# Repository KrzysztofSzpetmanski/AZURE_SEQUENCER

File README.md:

# AZURE_SEQUENCER

Firmware workspace for the AZURE Eurorack module based on Raspberry Pi Pico 2 (RP2350).

Current firmware build: `2.003`

## Current Apps

- `CALIBRATION` - 4-point DAC calibration with two ranges: `-3..+7V` and `0..+10V`
- `NOTES` - calibration point summary view
- `VOLTS` - calibration range and point voltage view
- `GRIDS` - Mutable Grids-style trigger engine with parameter menu and 32-step per-channel preview
- `TRIG SEQ` - trigger sequencer with grid editing, presets and clock options
- `4XEUCLID` - 4-channel Euclidean trigger generator with per-channel steps/hits
- `TR2GATE` - 4-channel trigger-to-gate converter with per-channel source/time/probability
- `TR2ADSR` - 4-channel trigger-to-envelope generator with AR/ASR/ADSR modes

## Build

```bash
cd /Users/lazuli/Documents/PROGRAMMING/RSB_PICO/AZURE_SEQUENCER
cmake -S . -B build
cmake --build build -j4
```

Artifacts:

- `build/hrdw_test.elf`
- `build/hrdw_test.uf2`

## Flash

Standard Pico UF2 drag-and-drop flow:

1. Hold BOOTSEL while connecting Pico 2 via USB.
2. Copy `build/hrdw_test.uf2` to the mounted RPI-RP2 drive.

## Project Structure

- `src/hrdw_test.c` - app loop, UI, app state machines
- `src/hal_io.*` - OLED, encoders, buttons, DAC I/O
- `src/firmware_version.h` - AZURE firmware build label shown in the main menu
- `src/hal_mux_adc.*` - CV MUX ADC input handling
- `src/clock_input.*` - TR1 GPIO IRQ clock event queue and diagnostics
- `src/trigger_output.*` - shared us-based trigger/gate pulse scheduler
- `src/calibration.*` - calibration model + flash persistence
- `src/grids_engine.*` - Grids trigger generation core
- `src/trigseq_engine.*` - trigger sequencer core
- `src/app_settings.*` - app settings persistence
- `hardware/` - KiCad schematic and PCB

## Timing Notes

External clock on `TR1` is timestamped in a GPIO IRQ and delivered to apps through a small event queue. `TRIG SEQ`, `4XEUCLID`, `GRIDS`, and `BURST GEN` consume those events via `*_on_clock_tick(timestamp_us)` style dispatch instead of polling for the clock edge in their UI/update code.

Trigger and burst pulse widths are scheduled in microseconds by the shared trigger output engine. Timing accuracy is limited by MCP4728 I2C update latency; firmware minimizes jitter by using IRQ timestamping, cached output states and batched DAC writes. The DAC bus defaults to 400 kHz via `DAC_I2C_BAUDRATE` in `src/hal_io.c`; set it back to 100000 if a hardware build has marginal pull-ups or bus stability issues.

Pulse OFF service is driven by a 500 us repeating timer flag and serviced from the foreground timing path before OLED/UI work. The timer callback does not write I2C directly; MCP4728 writes stay out of IRQ context.

Optional 1 Hz timing diagnostics can be enabled with `ENABLE_TIMING_DIAG_PRINT` in `src/hrdw_test.c`. The diagnostics include clock IRQ count, ignored edges, queue overflow, measured BPM, max clock-event latency, max trigger-fire latency, DAC write/skip counters, and max OLED frame time.

## Hardware Timing Test Plan

1. Feed a stable master clock or FH-2 clock into `TR1`.
2. Set `TRIG SEQ` to 16 steps with hits on 1/5/9/13.
3. On an oscilloscope, measure `TR1` edge to output trigger latency, pulse width, and jitter while OLED is active and encoders are moved.
4. Test `4XEUCLID` with a stable `4/16` pattern and verify even output spacing.
5. Test `GRIDS` while changing CV/fill; CV sampling should not disturb clock-edge timing.
6. Test fast `BURST GEN` patterns; pulses should not merge or disappear except within MCP4728/I2C limits.
7. Compare DAC/I2C stability at 400 kHz versus 100 kHz if the bus shows artifacts.

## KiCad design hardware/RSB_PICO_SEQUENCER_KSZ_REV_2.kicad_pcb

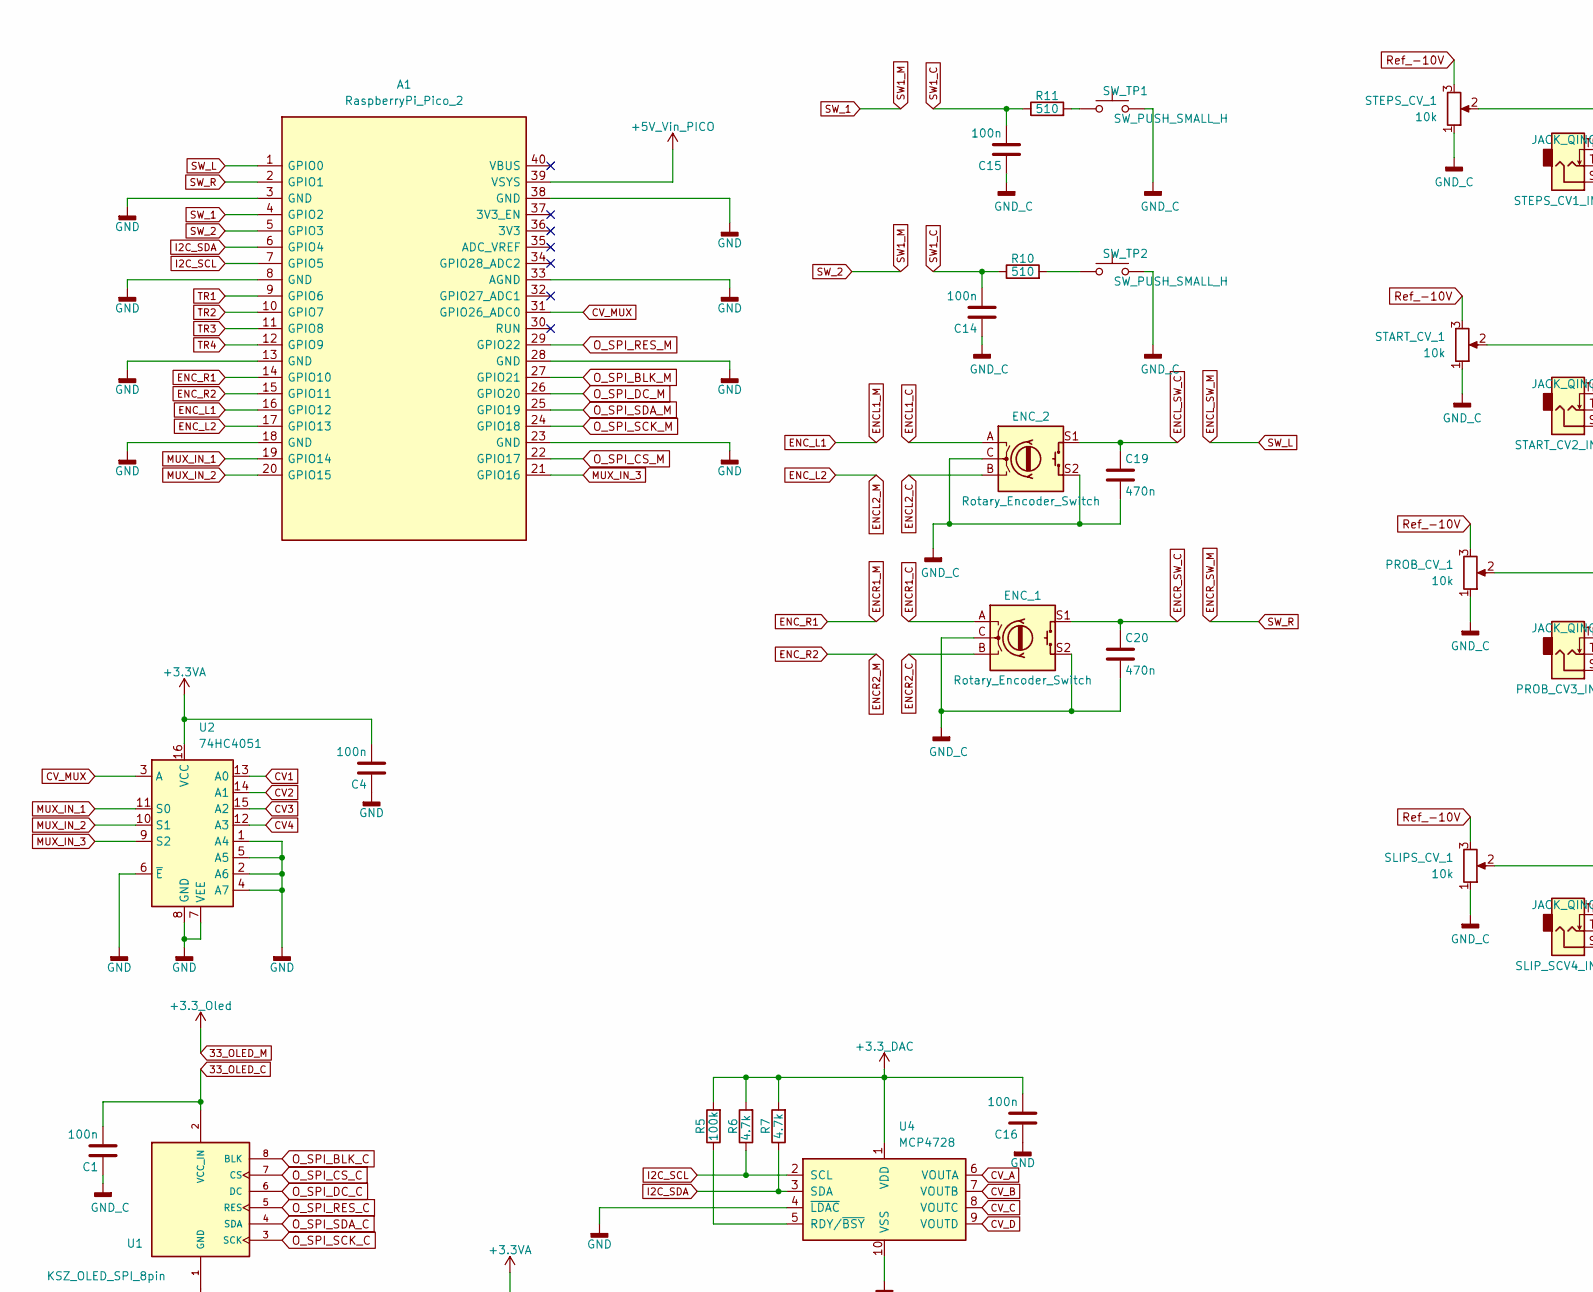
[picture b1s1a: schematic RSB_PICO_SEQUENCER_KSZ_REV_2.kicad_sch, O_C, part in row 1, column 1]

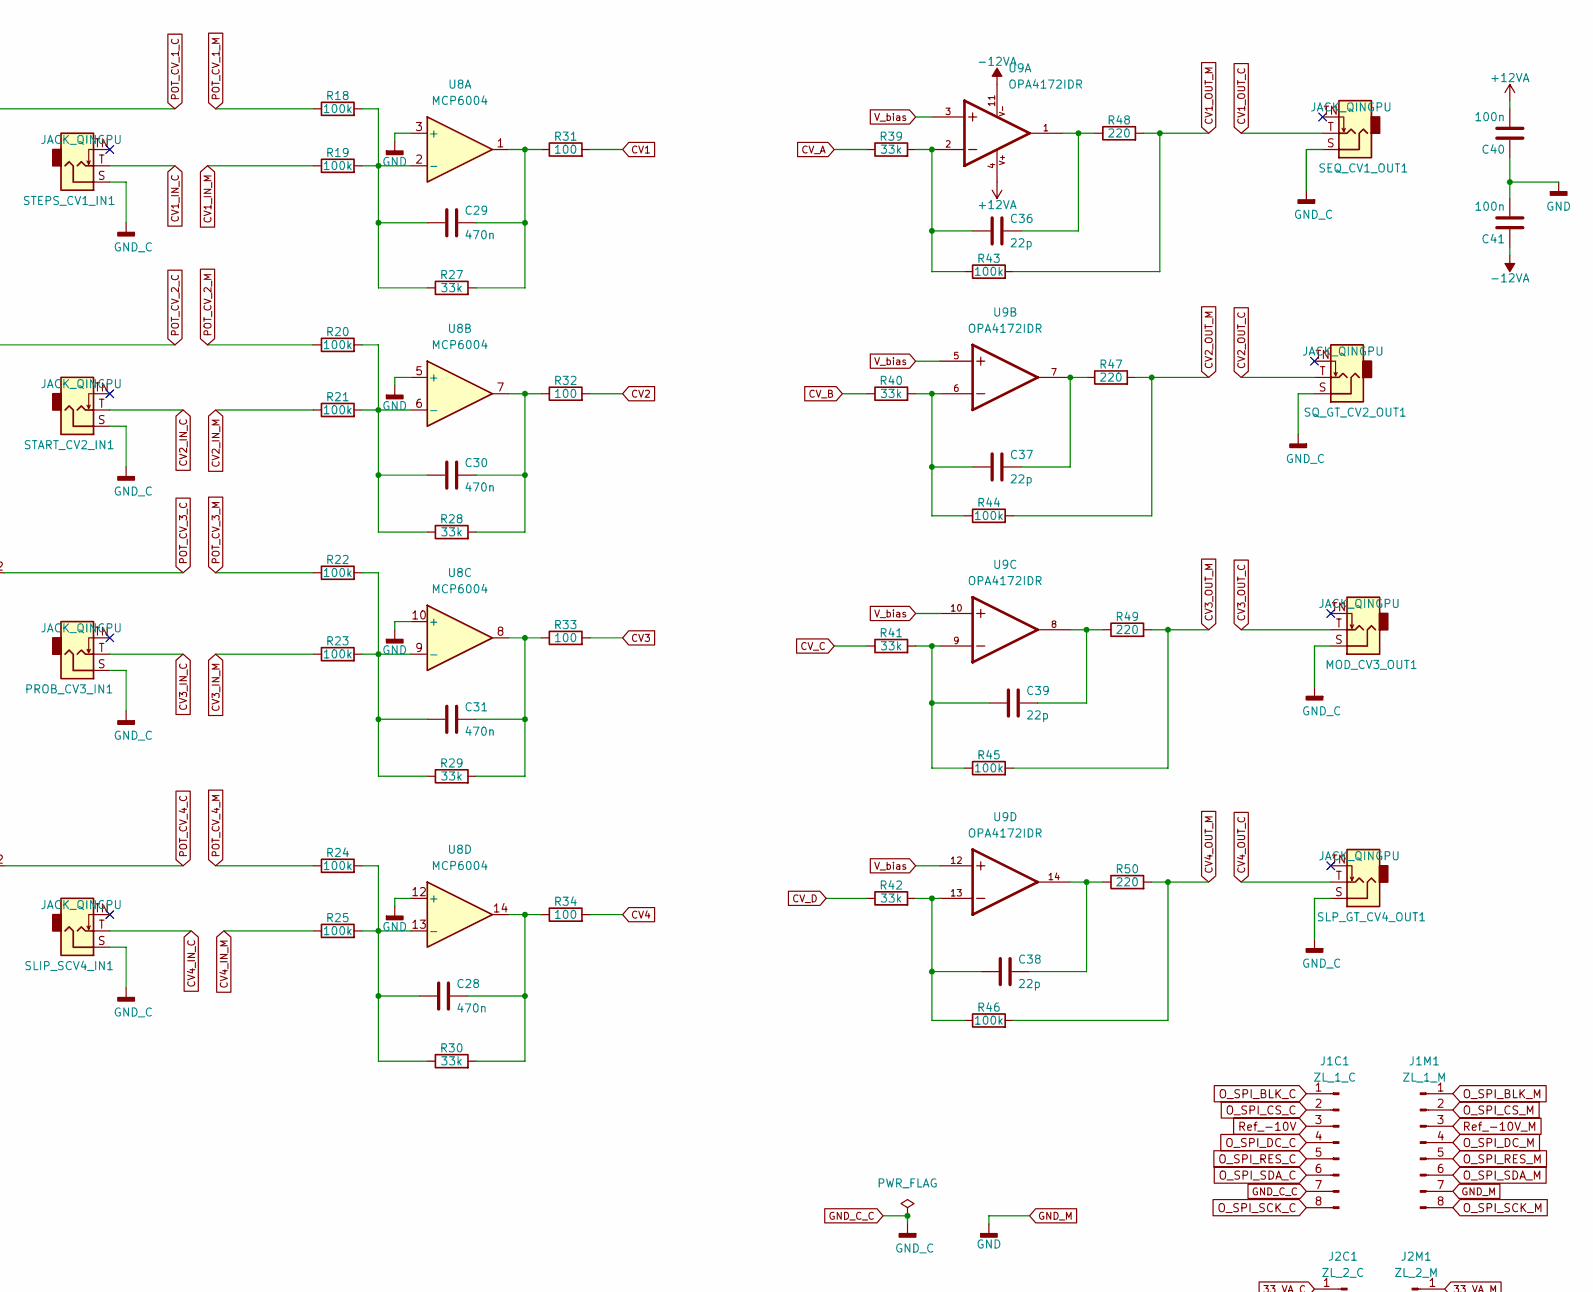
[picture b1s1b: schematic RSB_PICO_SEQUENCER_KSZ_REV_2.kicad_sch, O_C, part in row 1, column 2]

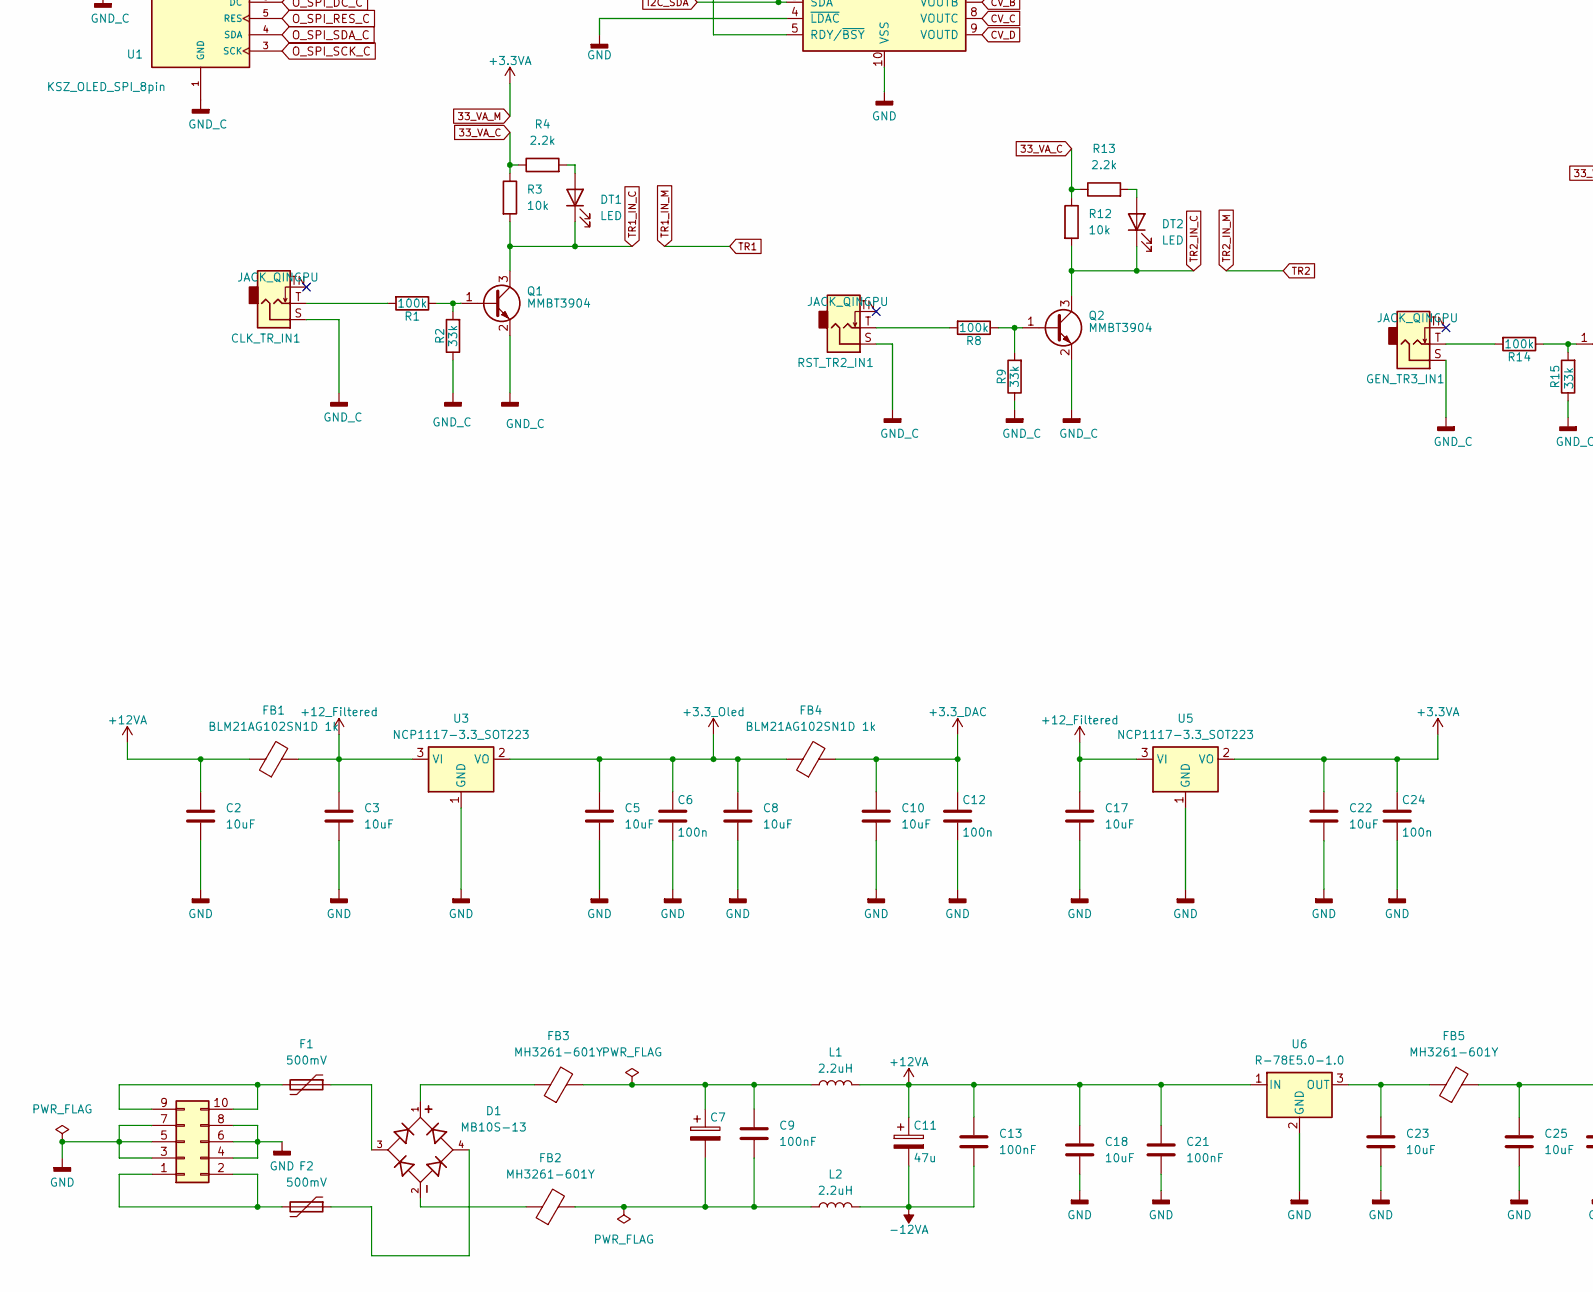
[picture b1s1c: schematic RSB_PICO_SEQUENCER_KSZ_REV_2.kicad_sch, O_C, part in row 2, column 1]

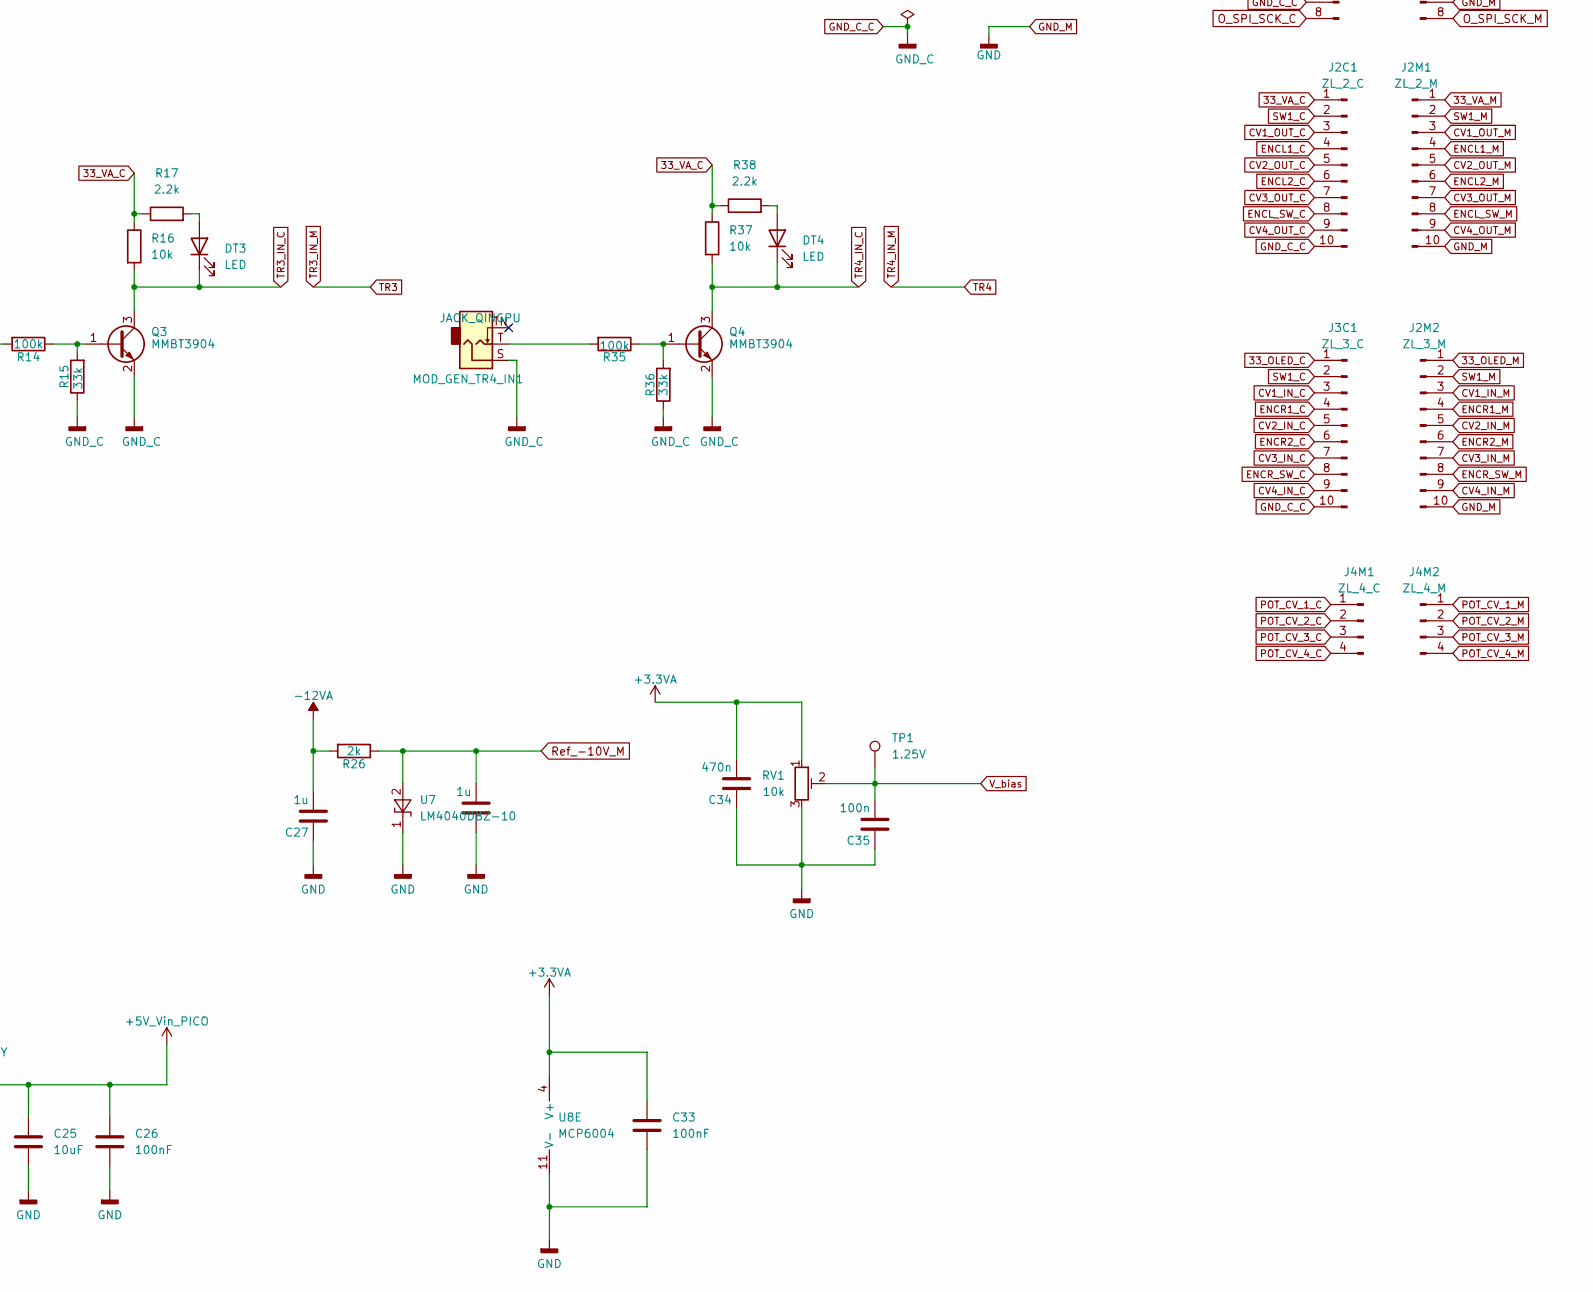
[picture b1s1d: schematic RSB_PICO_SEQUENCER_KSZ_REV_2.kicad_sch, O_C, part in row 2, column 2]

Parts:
A1: RaspberryPi_Pico_2; RaspberryPi_Pico_2_KSZ
C1, C4, C14, C15, C16, C35, C40, C41: 100n; C_0603_1608Metric_Pad1.08x0.95mm_HandSolder; MPN C0603C104Z3VACTU
C2, C3, C5, C8, C10, C17, C18, C22, C23, C25: 10uF; C_1206_3216Metric_Pad1.33x1.80mm_HandSolder
C6, C12, C24: 100n; C_0603_1608Metric_Pad1.08x0.95mm_HandSolder; MPN C0603C104Z3VACTU; LCSC C49678
C7, C11: 47u; CP_Radial_D5.0mm_P2.00mm; MPN EEF-CX1D220R
C9, C13, C21, C26, C33: 100nF; C_0603_1608Metric_Pad1.08x0.95mm_HandSolder; LCSC C49678
C19, C20, C28, C29, C30, C31, C34: 470n; C_0603_1608Metric_Pad1.08x0.95mm_HandSolder; MPN EMK107B7474KA-T
C27, C32: 1u; C_0603_1608Metric_Pad1.08x0.95mm_HandSolder; MPN GCJ188R71E105KA01D
C36, C37, C38, C39: 22p; C_0603_1608Metric_Pad1.08x0.95mm_HandSolder; MPN C0603C220J5GACTU
CLK_TR_IN1: JACK_QINGPU; Jack_3.5mm_tip_switch_thonkiconn
D1: MB10S-13; SOIC245P670X290-4N
DT1, DT2, DT3, DT4: LED; LED_D3.0mm
ENC_1, ENC_2: Rotary_Encoder_Switch; RotaryEncoder_Bourns-PEC11R-4xxxF-Sxxxx-Switch_Vertical_H20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; MPN PEC11S-9215K-H0015
F1, F2: 500mV; C_Disc_D5.0mm_W2.5mm_P5.00mm
FB1, FB4: BLM21AG102SN1D 1k; L_0805_2012Metric_Pad1.05x1.20mm_HandSolder
FB2, FB3, FB5: MH3261-601Y; L_1206_3216Metric
GEN_TR3_IN1: JACK_QINGPU; Jack_3.5mm_tip_switch_thonkiconn
J1: Bus_Power; Power_Header
J1C1: ZL_1_C; PinSocket_1x08_P2.54mm_Vertical
J1M1: ZL_1_M; PinSocket_1x08_P2.54mm_Vertical
J2C1: ZL_2_C; PinHeader_1x10_P2.54mm_Vertical
J2M1: ZL_2_M; PinHeader_1x10_P2.54mm_Vertical
J2M2: ZL_3_M; PinHeader_1x10_P2.54mm_Vertical
J3C1: ZL_3_C; PinHeader_1x10_P2.54mm_Vertical
J4M1: ZL_4_C; PinHeader_1x04_P2.54mm_Vertical
J4M2: ZL_4_M; PinHeader_1x04_P2.54mm_Vertical
L1, L2: 2.2uH; L_1008_2520Metric_Pad1.43x2.20mm_HandSolder
MOD_CV3_OUT1: JACK_QINGPU; Jack_3.5mm_tip_switch_thonkiconn
MOD_GEN_TR4_IN1: JACK_QINGPU; Jack_3.5mm_tip_switch_thonkiconn
PROB_CV3_IN1: JACK_QINGPU; Jack_3.5mm_tip_switch_thonkiconn
PROB_CV_1: 10k; Potentiometer_Alpha_RD901F-40-00D_Single_Vertical_centered
Q1, Q2, Q3, Q4: MMBT3904; SOT-23; MPN MMBT3904,215
R1, R8, R14, R19, R21, R23, R25, R35, R43, R44, R45, R46: 100k; R_0603_1608Metric_Pad0.98x0.95mm_HandSolder; MPN RCA0603100KJNEC
R2, R9, R15, R27, R28, R29, R30, R36: 33k; R_0603_1608Metric_Pad0.98x0.95mm_HandSolder; MPN ERJ-3GEYJ333V
R3, R12, R16, R37: 10k; R_0603_1608Metric_Pad0.98x0.95mm_HandSolder
R4, R13, R17, R38: 2.2k; R_0603_1608Metric_Pad0.98x0.95mm_HandSolder
R5, R18, R20, R22, R24: 100k; R_0603_1608Metric_Pad0.98x0.95mm_HandSolder; MPN CR0603-FX-2202ELF
R6, R7: 4.7k; R_0603_1608Metric_Pad0.98x0.95mm_HandSolder; MPN CR0603-FX-2202ELF
R10, R11: 510; R_0603_1608Metric_Pad0.98x0.95mm_HandSolder; MPN RC0603FR-07510RL
R26: 2k; R_0603_1608Metric_Pad0.98x0.95mm_HandSolder; MPN RC0603FR-0724K9L
R31, R32, R33, R34: 100; R_0603_1608Metric_Pad0.98x0.95mm_HandSolder
R39, R40, R41, R42: 33k; R_0603_1608Metric_Pad0.98x0.95mm_HandSolder; MPN RC0603FR-0724K9L
R47, R48, R49, R50: 220; R_0603_1608Metric_Pad0.98x0.95mm_HandSolder; MPN CRCW0603220RFKEB
RST_TR2_IN1: JACK_QINGPU; Jack_3.5mm_tip_switch_thonkiconn
RV1: 10k; Potentiometer_Bourns_3296W_Vertical_screw_centered
SEQ_CV1_OUT1: JACK_QINGPU; Jack_3.5mm_tip_switch_thonkiconn
SLIPS_CV_1: 10k; Potentiometer_Alpha_RD901F-40-00D_Single_Vertical_centered
SLIP_SCV4_IN1: JACK_QINGPU; Jack_3.5mm_tip_switch_thonkiconn
SLP_GT_CV4_OUT1: JACK_QINGPU; Jack_3.5mm_tip_switch_thonkiconn
SQ_GT_CV2_OUT1: JACK_QINGPU; Jack_3.5mm_tip_switch_thonkiconn
START_CV2_IN1: JACK_QINGPU; Jack_3.5mm_tip_switch_thonkiconn
START_CV_1: 10k; Potentiometer_Alpha_RD901F-40-00D_Single_Vertical_centered
STEPS_CV1_IN1: JACK_QINGPU; Jack_3.5mm_tip_switch_thonkiconn
STEPS_CV_1: 10k; Potentiometer_Alpha_RD901F-40-00D_Single_Vertical_centered
SW_TP1, SW_TP2: SW_PUSH_SMALL_H; SW_PUSH_6mm; MPN ADTSM66NV
TP1: 1.25V; TestPoint_THTPad_D1.5mm_Drill0.7mm
U1: KSZ_OLED_SPI_8pin; TFT_18cala_128x160_8pin_KSZ; PARTREV 2018-09-10
U2: 74HC4051; SOIC-16_3.9x9.9mm_P1.27mm
U3, U5: NCP1117-3.3_SOT223; SOT-223-3_TabPin2
U4: MCP4728; MSOP-10-1EP_3x3mm_P0.5mm_EP1.68x1.88mm
U6: R-78E5.0-1.0; Converter_DCDC_RECOM_R-78E-0.5_THT
U7: LM4040DBZ-10; SOT-23
U8: MCP6004; SOIC-14_3.9x8.7mm_P1.27mm
U9: OPA4172IDR; SOIC-14_3.9x8.7mm_P1.27mm; PARTREV I

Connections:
33_OLED_C: C1.2, J3C1.1, U1.2 (VCC_IN)
33_OLED_M: C5.1, C6.1, C8.1, FB4.1, J2M2.1, U3.2 (VO)
33_VA_C: J2C1.1, R3.1, R4.1, R12.1, R13.1, R16.1, R17.1, R37.1, R38.1
33_VA_M: C4.2, C22.1, C24.1, C33.1, C34.2, J2M1.1, RV1.1, U2.16 (VCC), U5.2 (VO), U8.4 (V+)
+3.3_DAC: C10.1, C12.1, C16.2, FB4.2, R5.2, R6.2, R7.2, U4.1 (VDD)
+5V_Vin_PICO: A1.39 (VSYS), C25.1, C26.1, FB5.2
+12VA: C2.1, C11.1, C13.1, C18.1, C21.1, C40.2, FB1.1, L1.2, U6.1 (IN), U9.4
+12_Filtered: C3.1, C17.1, FB1.2, U3.3 (VI), U5.3 (VI)
-12VA: C11.2, C13.2, C27.2, C41.1, L2.2, R26.2, U9.11
CV1: R31.2, U2.13 (A0)
CV1_IN_C: J3C1.3, STEPS_CV1_IN1.T
CV1_IN_M: J2M2.3, R19.1
CV1_OUT_C: J2C1.3, SEQ_CV1_OUT1.T
CV1_OUT_M: J2M1.3, R43.2, R48.2
CV2: R32.2, U2.14 (A1)
CV2_IN_C: J3C1.5, START_CV2_IN1.T
CV2_IN_M: J2M2.5, R21.1
CV2_OUT_C: J2C1.5, SQ_GT_CV2_OUT1.T
CV2_OUT_M: J2M1.5, R44.2, R47.2
CV3: R33.2, U2.15 (A2)
CV3_IN_C: J3C1.7, PROB_CV3_IN1.T
CV3_IN_M: J2M2.7, R23.1
CV3_OUT_C: J2C1.7, MOD_CV3_OUT1.T
CV3_OUT_M: J2M1.7, R45.2, R49.2
CV4: R34.2, U2.12 (A3)
CV4_IN_C: J3C1.9, SLIP_SCV4_IN1.T
CV4_IN_M: J2M2.9, R25.1
CV4_OUT_C: J2C1.9, SLP_GT_CV4_OUT1.T
CV4_OUT_M: J2M1.9, R46.2, R50.2
CV_A: R39.1, U4.6 (VOUTA)
CV_B: R40.1, U4.7 (VOUTB)
CV_C: R41.1, U4.8 (VOUTC)
CV_D: R42.1, U4.9 (VOUTD)
CV_MUX: A1.31 (GPIO26_ADC0), U2.3 (A)
ENCL1_C: ENC_2.A, J2C1.4
ENCL1_M: A1.16 (GPIO12), J2M1.4
ENCL2_C: ENC_2.B, J2C1.6
ENCL2_M: A1.17 (GPIO13), J2M1.6
ENCL_SW_C: C19.1, ENC_2.S1, J2C1.8
ENCL_SW_M: A1.1 (GPIO0), J2M1.8
ENCR1_C: ENC_1.A, J3C1.4
ENCR1_M: A1.14 (GPIO10), J2M2.4
ENCR2_C: ENC_1.B, J3C1.6
ENCR2_M: A1.15 (GPIO11), J2M2.6
ENCR_SW_C: C20.1, ENC_1.S1, J3C1.8
ENCR_SW_M: A1.2 (GPIO1), J2M2.8
GND_C_C: C1.1, C14.1, C15.1, C19.2, C20.2, CLK_TR_IN1.S, ENC_1.C, ENC_1.S2, ENC_2.C, ENC_2.S2, GEN_TR3_IN1.S, J1C1.7, J2C1.10, J3C1.10, MOD_CV3_OUT1.S, MOD_GEN_TR4_IN1.S, PROB_CV3_IN1.S, PROB_CV_1.1, Q1.2 (E), Q2.2 (E), Q3.2 (E), Q4.2 (E), R2.1, R9.1, R15.1, R36.1, RST_TR2_IN1.S, SEQ_CV1_OUT1.S, SLIPS_CV_1.1, SLIP_SCV4_IN1.S, SLP_GT_CV4_OUT1.S, SQ_GT_CV2_OUT1.S, START_CV2_IN1.S, START_CV_1.1, STEPS_CV1_IN1.S, STEPS_CV_1.1, SW_TP1.2, SW_TP2.2, U1.1 (GND)
GND_M: A1.3 (GND), A1.8 (GND), A1.13 (GND), A1.18 (GND), A1.23 (GND), A1.28 (GND), A1.33 (AGND), A1.38 (GND), C2.2, C3.2, C4.1, C5.2, C6.2, C8.2, C10.2, C12.2, C16.1, C17.2, C18.2, C21.2, C22.2, C23.2, C24.2, C25.2, C26.2, C27.1, C32.1, C33.2, C34.1, C35.1, C40.1, C41.2, J1.3, J1.4, J1.5, J1.6, J1.7, J1.8, J1M1.7, J2M1.10, J2M2.10, RV1.3, U2.1 (A4), U2.2 (A6), U2.4 (A7), U2.5 (A5), U2.6 (~E), U2.7 (VEE), U2.8 (GND), U3.1 (GND), U4.4 (~LDAC), U4.10 (VSS), U5.1 (GND), U6.2 (GND), U7.1 (K), U8.3 (+), U8.5 (+), U8.10 (+), U8.11 (V-), U8.12 (+)
I2C_SCL: A1.7 (GPIO5), R6.1, U4.2 (SCL)
I2C_SDA: A1.6 (GPIO4), R7.1, U4.3 (SDA)
MUX_IN_1: A1.19 (GPIO14), U2.11 (S0)
MUX_IN_2: A1.20 (GPIO15), U2.10 (S1)
MUX_IN_3: A1.21 (GPIO16), U2.9 (S2)
unnamed: C7.1, C9.1, FB3.2, L1.1
unnamed: C7.2, C9.2, FB2.2, L2.1
unnamed: C28.1, R30.2, R34.1, U8.14
unnamed: C29.1, R27.2, R31.1, U8.1
unnamed: C30.1, R28.2, R32.1, U8.7
unnamed: C31.1, R29.2, R33.1, U8.8
unnamed: C36.1, R48.1, U9.1
unnamed: C36.2, R39.2, R43.1, U9.2
unnamed: C37.1, R47.1, U9.7
unnamed: C37.2, R40.2, R44.1, U9.6
unnamed: C38.1, R50.1, U9.14
unnamed: C38.2, R42.2, R46.1, U9.13
unnamed: C39.1, R49.1, U9.8
unnamed: C39.2, R41.2, R45.1, U9.9
unnamed: CLK_TR_IN1.T, R1.2
unnamed: D1.1, FB3.1
unnamed: D1.2, FB2.1
unnamed: D1.3, F1.1
unnamed: D1.4, F2.1
unnamed: DT1.2 (A), R4.2
unnamed: DT2.2 (A), R13.2
unnamed: DT3.2 (A), R17.2
unnamed: DT4.2 (A), R38.2
unnamed: GEN_TR3_IN1.T, R14.2
unnamed: F2.2, J1.1, J1.2
unnamed: F1.2, J1.9, J1.10
unnamed: MOD_GEN_TR4_IN1.T, R35.2
unnamed: Q1.1 (B), R1.1, R2.2
unnamed: Q2.1 (B), R8.1, R9.2
unnamed: Q3.1 (B), R14.1, R15.2
unnamed: Q4.1 (B), R35.1, R36.2
unnamed: R8.2, RST_TR2_IN1.T
unnamed: R10.2, SW_TP2.1
unnamed: R11.2, SW_TP1.1
unnamed: R5.1, U4.5 (RDY/~BSY)
unnamed: C23.1, FB5.1, U6.3 (OUT)
unnamed: C29.2, R18.2, R19.2, R27.1, U8.2 (-)
unnamed: C30.2, R20.2, R21.2, R28.1, U8.6 (-)
unnamed: C31.2, R22.2, R23.2, R29.1, U8.9 (-)
unnamed: C28.2, R24.2, R25.2, R30.1, U8.13 (-)
O_SPI_BLK_C: J1C1.1, U1.8 (BLK)
O_SPI_BLK_M: A1.27 (GPIO21), J1M1.1
O_SPI_CS_C: J1C1.2, U1.7 (CS)
O_SPI_CS_M: A1.22 (GPIO17), J1M1.2
O_SPI_DC_C: J1C1.4, U1.6 (DC)
O_SPI_DC_M: A1.26 (GPIO20), J1M1.4
O_SPI_RES_C: J1C1.5, U1.5 (RES)
O_SPI_RES_M: A1.29 (GPIO22), J1M1.5
O_SPI_SCK_C: J1C1.8, U1.3 (SCK)
O_SPI_SCK_M: A1.24 (GPIO18), J1M1.8
O_SPI_SDA_C: J1C1.6, U1.4 (SDA)
O_SPI_SDA_M: A1.25 (GPIO19), J1M1.6
POT_CV_1_C: J4M1.1, STEPS_CV_1.2
POT_CV_1_M: J4M2.1, R18.1
POT_CV_2_C: J4M1.2, START_CV_1.2
POT_CV_2_M: J4M2.2, R20.1
POT_CV_3_C: J4M1.3, PROB_CV_1.2
POT_CV_3_M: J4M2.3, R22.1
POT_CV_4_C: J4M1.4, SLIPS_CV_1.2
POT_CV_4_M: J4M2.4, R24.1
Ref_-10V: J1C1.3, PROB_CV_1.3, SLIPS_CV_1.3, START_CV_1.3, STEPS_CV_1.3
Ref_-10V_M: C32.2, J1M1.3, R26.1, U7.2 (A)
SW1_C: C14.2, C15.2, J2C1.2, J3C1.2, R10.1, R11.1
SW1_M: A1.4 (GPIO2), A1.5 (GPIO3), J2M1.2, J2M2.2
TR1: A1.9 (GPIO6)
TR1_IN_C: DT1.1 (K), Q1.3 (C), R3.2
TR2: A1.10 (GPIO7)
TR2_IN_C: DT2.1 (K), Q2.3 (C), R12.2
TR3: A1.11 (GPIO8)
TR3_IN_C: DT3.1 (K), Q3.3 (C), R16.2
TR4: A1.12 (GPIO9)
TR4_IN_C: DT4.1 (K), Q4.3 (C), R37.2
V_bias: C35.2, RV1.2, TP1.1, U9.3, U9.5, U9.10, U9.12

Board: 2 copper layers, 150 parts (8 on the bottom side), 122 nets, no tracks yet.

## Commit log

2026-05-24 Add hardware test menu, GRIDS/TRIGSEQ apps, and persistent app settings
2026-05-26 Finalize UI fixes and add project documentation
2026-05-28 Add per-channel probability controls to TRIGSEQ and 4XEUCLID
2026-06-04 Add CV GEN and preset support
2026-06-06 Stabilize timing and show firmware build
2026-06-06 Add IRQ trigger edges and smooth burst UI
